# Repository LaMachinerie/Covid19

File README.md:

# Covid19
Ce projet à pour but de rendre accessible les ressources de l'association amiènoise La Machinerie afin de lutter contre la pandémie.

Aux côtés d'autres collectifs à Amiens et ailleurs, La Machinerie et sa communauté souhaitent contribuer, via la production de visières de protection dans le cadre de la lutte contre le COVID 19. Nous invitons les structures et les makers qui souhaitent eux aussi apporter leur aide dans cette entreprise à nous contacter s'ils le souhaitent.

Pour plus d'informations, visiter : (https://entraide-amiens-covid.lamachinerie.org/)

Les fichiers partagés ici ont été developpés par la communauté "Entraide Maker National"

# Sources
### Nationnal

Lien vers le Groupe Discord national "Entraide Maker - COVID 19" : [cliquez-ici](https://www.google.com/url?q=https%3A%2F%2Ft.co%2FKCWUXKPz0U%3Famp%3D1&sa=D&sntz=1&usg=AFQjCNEH4NNZD81Wm58awYNpvExc2nMsbw)

Lien vers les Visières validées par le projet "Entraide Maker - COVID 19" : [cliquez-ici](https://www.google.com/url?q=https%3A%2F%2Fgitlab.com%2Fentraide-maker-covid-19%2Fvisieres&sa=D&sntz=1&usg=AFQjCNEOhtFKottFw5Ar9eYx8JXE-eFxSA)

Lien vers la documentation de production par le RFFLab: [cliquez-ici](http://www.google.com/url?q=http%3A%2F%2Fwww.fablab.fr%2Fcoronavirus%2Fprototypage-et-projets%2Farticle%2F2-visieres-de-protection-coronavirus&sa=D&sntz=1&usg=AFQjCNHDDo52mAoGNO2gYDtjmfGWl7S11Q)

Site Covid - Initiatives pour recenser les initiatives au niveau national [cliquez-ici](https://www.google.com/url?q=https%3A%2F%2Fcovid-initiatives.org&sa=D&sntz=1&usg=AFQjCNGfX7_Z7UGRu0mLkms393UgGfVRuw)

Site Visières Solidaires : (https://visieresolidaire.org/fr/)

### L'Electrolab :

Site internet de l'electrolab [cliquez-ici](https://www.google.com/url?q=https%3A%2F%2Fwww.electrolab.fr&sa=D&sntz=1&usg=AFQjCNHCNd2qVjSVs_PJbtIoONKtBqdbrg)

Gitlab pour le projet de visière de l'electrolab[cliquez-ici](https://www.google.com/url?q=https%3A%2F%2Fcode.electrolab.fr%2Fcovid-19%2Fvisiere&sa=D&sntz=1&usg=AFQjCNFIvQYNNAXeBKP6lAQ21kB8IrkSCw)

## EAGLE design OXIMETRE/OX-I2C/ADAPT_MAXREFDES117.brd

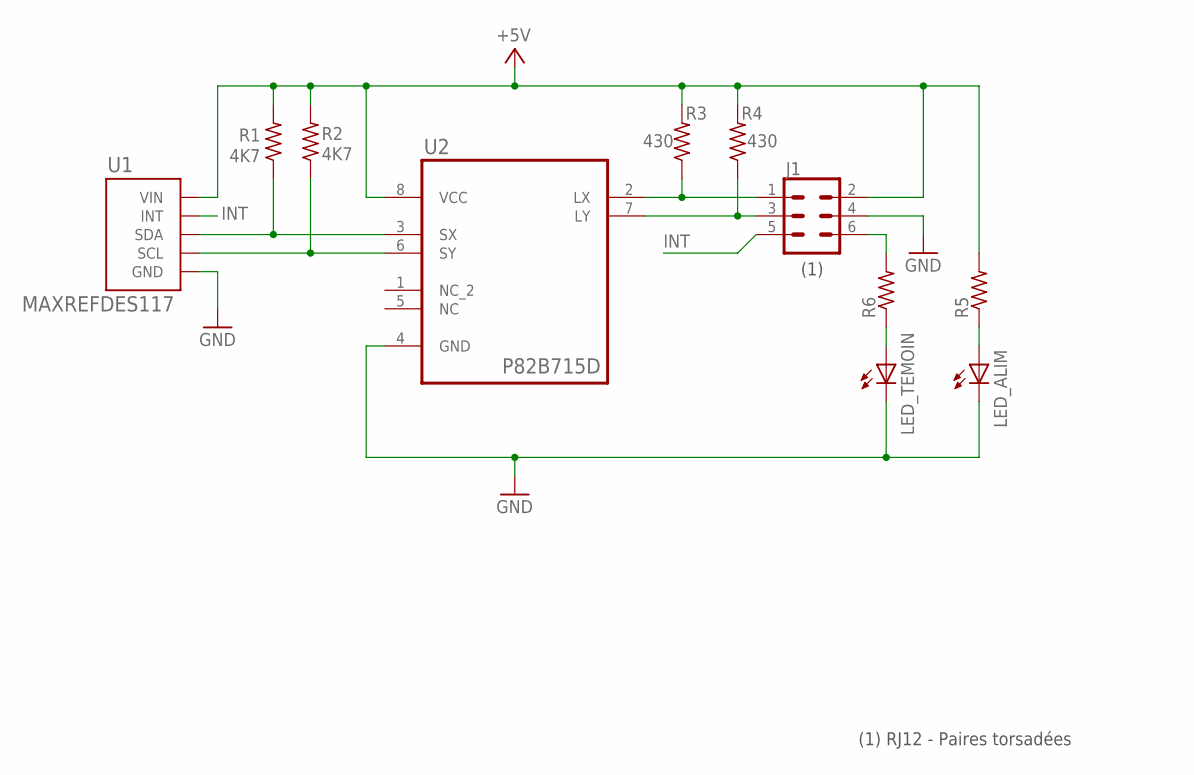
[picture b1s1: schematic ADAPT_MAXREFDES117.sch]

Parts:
J1: CONN_03X2NO_SILK; 2X3-NS
LED_ALIM: LEDFAB1206; LED1206FAB
LED_TEMOIN: LEDFAB1206; LED1206FAB
R1, R2: 4K7; R1206FAB
R3, R4: 430; R1206FAB
R5, R6: RES-US1206FAB; R1206FAB
U1: MAXREFDES117
U2: P82B715D; SOIC127P600X175-8N

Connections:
+5V: J1.2, R1.2, R2.2, R3.2, R4.2, R5.2, U1.VIN, U2.8 (VCC)
GND: J1.4, LED_ALIM.2 (C), LED_TEMOIN.2 (C), U1.GND, U2.4 (GND)
INT: J1.5, U1.INT$1 (INT), U1.INT$2 (INT)
unnamed: R1.1, U1.SDA$1 (SDA), U1.SDA$2 (SDA), U2.3 (SX)
unnamed: R2.1, U1.SCL$1 (SCL), U1.SCL$2 (SCL), U2.6 (SY)
unnamed: J1.1, R3.1, U2.2 (LX)
unnamed: LED_TEMOIN.1 (A), R6.1
unnamed: LED_ALIM.1 (A), R5.1
unnamed: J1.3, R4.1, U2.7 (LY)
unnamed: J1.6, R6.2

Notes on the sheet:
(1) RJ12 - Paires torsadées
(1)

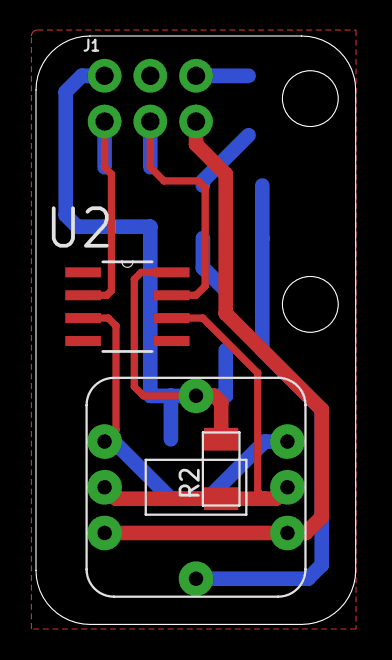
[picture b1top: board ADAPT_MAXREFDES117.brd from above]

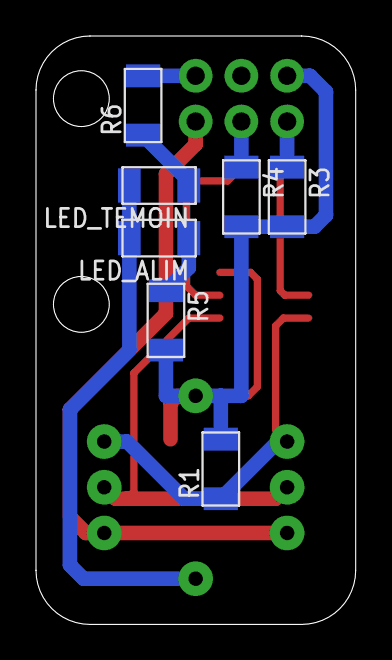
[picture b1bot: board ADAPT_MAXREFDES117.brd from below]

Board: 2 copper layers, 17.8 x 32.7 mm, 11 parts (7 on the bottom side), 10 nets.

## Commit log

2020-04-03 new version
    nouvelle version disponible sur le gitlab Entraide Maker - COVID 19
2020-04-18 first update
2020-04-18 first up
2020-04-18 first upload
2020-04-20 init(Firmware) : Initialize the firmware project
2020-04-21 clean( afe44xx) clean-up by creating .h .cpp for Afe44xx library
2020-04-21 feat(afe44xx) : Add debug option for pre-compiler
2020-04-22 feat(Maxim) : Add Maxim sensor library
2020-04-22 clean(Global) : Clean things
2020-04-23 Fixing things... Too much...
2020-04-24 :sparkles: New pictures
2020-04-24 :sparkles: minor update
